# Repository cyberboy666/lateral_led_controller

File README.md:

# lateral_led_controller

### hardware network controller for addressable led installations 

- this circuit is distributed by __UNDERSCORES__ - _an open video hardware label_ : it is available to purchase - as a pcb, kit or assembled unit - at [underscores.shop](https://underscores.shop/lateral_led_controller/)
- the schematic for the circuit can be found [here](/hardware/schematic.pdf)
- the pcb gerber files for the lastest version can be found [here](/hardware/gerber_latest.zip)
- interactive BOM is [here](https://htmlpreview.github.io/?https://github.com/cyberboy666/lateral_led_controller/blob/main/hardware/bom/ibom.html)
- consider [donating](https://opencollective.com/underscores) to the underscores project to help us continue creating for the commons

## description

_lateral_led_controller_ is a hardware interface that converts [Art-Net](https://art-net.org.uk/), a network protocol for transmitting DMX data over network, into signals that drive addressable LEDs. it can be combined with mapping software (such as my [artnet_led_mapper](https://github.com/cyberboy666/artnet_led_mapper/)) to send arbitrary video onto an led strip canvas

features include:

- receives artnet data via ETHERNET, WIFI or ACCESS_POINT
- natively drive addressable leds [WS281X](https://www.aliexpress.com/item/4001322411818.html) and [APA102](https://www.aliexpress.com/item/32322326979.html)
- supports up to `8` parallel data outs and up to `12` DMX universes for max control over `2000` leds !
- local web interface for easily configuring network / led settings
- flexible dc power input - between 5v to 12v with low-heat / efficient on-board step-down converter
- open source hardware and firmware - can be customized to meet your specific needs

## background

this controller is a companion to my [artnet_led_mapper](https://github.com/cyberboy666/artnet_led_mapper/) application that converts a video feed into artnet for addressable led strip installations. it was built for [lateral movement](https://cyberboy666.com/lateralmovement/) club nights such as seen here:

you can find some more background on this install and process here: [WORKS IN PROGRESS 04 - talk about controlling addressable leds for art installation](https://videos.scanlines.xyz/w/p/tUhDfYqJJPfjovscNMvFRL) 

## demo video

## hardware options

<details><summary>hardware options</summary>

besides this controller there are some more bits of hardware you will need to realize an _addressable led installation_ - i will outline some suggestions here based on my experience but this will depend on your specific requirements - feel free to [email me](mailto:tim@cyberboy666.com) if you would like individual consulting on this.

### led strips

this controller is configured to support two types of addressable led strips (more can be added by firmware update):

### __WS281X__

ie [neopixels](https://www.adafruit.com/product/2541),  [WS2813 (5v) or WS2815 (12v)](https://www.aliexpress.com/item/4001322411818.html)

- these strips are cheapest - around 5usd for 60/m on aliexpress
- data to them is sent over a single wire (D) but is quite slow (around _800kbps_)
- this means that a maximum of around 240 of these leds can be addressed in series before the refresh rate drops below 30fps
- this controller is designed to be able to address up to 8 seperate WS281X led strips in parallel (outputs D0-D7 on board) for maximum 1920 number of leds in total

### __APA102__

ie [dotstar](https://www.adafruit.com/product/2574) ,  [SK9822](https://www.aliexpress.com/item/32322326979.html)

- these strips cost more - around 10usd for 60/m on aliexpress
- data to them is sent over two wires : ( __D__ata and __C__lock ) but is _very fast_ - (around _24Mbps_ )
- the controller is designed to address a single APA10 led strip by connecting D0 -> Data, D1 -> Clock
- at those speeds there is no need to have parrallel outputs can easily address 2000 leds in series (may need to look into power injection tho)
- they also claim to draw around 1/5 of the power as WS281X (i havnt tested this myself)

## power supply

we ended up using a switching power supply [like this](https://www.aliexpress.com/item/1005002843829663.html) 

- choose voltage based on your strip type (likely to be either 5v or 12v)
- and then power based on the requirement for total number of leds you are using
- you should power the _lateral_led_controller_ from the same supply thats powering the leds (its designed to safely take 5v - 12v input) or atleast ensure the GNDs are connected
- take note on the recommended power wire thickness based on how much current is passing through it (if you use 12v strips then less current is required and therefore thinner wires)

## light diffusers

for most installation settings it is prefered to use some kind of diffuser to help to evenly distribute light. there are many options and information about this topic online

## wiring and connectors

the data lines from _lateral_led_controller_ uses Pluggable Screw Terminals - standard wire (22awg etc) can connect these lines from controller to the strip

theres also the option to use cat5/6 cables to carry multiple data lines from the _lateral_led_controller_ - these are quite cheap, come in long distances and have twisted pairs which should allow for longer runs

personally i prefer running power lines seperately (on [red+black paired wire](https://www.aliexpress.com/item/4000625095039.html) ) - and using [these kinds](https://www.aliexpress.com/item/1005004267277214.html) of barrel / screw connectors to easily plug in / unplug from the installation

most led strips come with these [SM JST 4](https://www.aliexpress.com/item/1005002516911742.html?) connectors pre-soldered to both ends. one option if you dont want to resolder wires / new connectors onto each strip would be to just get some extra of these and create breakouts

### custom adapter boards

i made two little pcb adatpers that may help you with format convertion also - see below for some examples of how you could wire them

</details>

## software options

<details><summary>software options</summary>

any software that can output artnet over a network can be used with _lateral_led_controller_. some programs i have tested it with include:

- my [artnet_led_mapper](https://github.com/cyberboy666/artnet_led_mapper) application
- [resolume](https://resolume.com/)
- [touch designer](https://derivative.ca/UserGuide/TouchDesigner)
- [QLC+](https://www.qlcplus.org/)

</details>

# documentation

this project is fully _open-source hardware_ - all the files required to build it are included in this repo for free. if you have the time and/or skill you can contribute back by collaborating on / testing new designs, improving these docs, making demo videos/other creative content etc. you can also support the project financially by [donating](https://opencollective.com/underscores) directing, or purchasing through the [web shop](https://underscores.shop).

depending on whether you are going fully diy or buying an assembled and tested unit, some of the following guides will be relavent to you. the flow would be:

## ordering parts

<details><summary><b>parts sourcing guide (w/ notes on pcb fabracation )</b> - start here if you are building fully from scatch or have purchased a pcb</summary>

i try to source all the parts i can from either:
- [tayda](https://www.taydaelectronics.com/) ; cheaper for common parts like resistors etc, also good for mechanical parts like switches and buttons
- [mouser](https://www.mouser.de/) ; has lots more options, speciality video ic's, can sometimes cost more (free shipping on orders over 50euros)
- other ; ocationally there will be parts which will need to be sourced elsewhere - usaully either aliexpress, ebay or amazon etc...

take a look at the [full_bom](/hardware/bom/full_bom.csv) for this project to see where i am sourcing each part from

## import into tayda

- go to the [tayda quick order](https://www.taydaelectronics.com/quick-order/) and in bottom corner choose _add from file_
- select the file [tayda_bom.csv](./hardware/bom/tayda_bom.csv) in the BOM folder (you will have to download it first or clone this repo)
- after importing select _add to cart_
- __NOTE:__ the minimum value for resistors is 10, so you may need to modify these values to add to cart (or if they are already modified here you will need to see the  full_bom for actual part QTY) 

- OPTIONAL: it is a good idea to add some dip-ic sockets and 2.54pin headers/sockets to your tayda order if you dont have them around already

## sourcing other parts

this circuit has a few _specific_ parts that can not be sourced from tayda/mouser:

### WT32-ETH01 micro-controller
we are using a [WT32-ETH01](https://www.aliexpress.com/item/1005007279607510.html) ESP32 controller with the LAN8720A chip / ethernet port already attached - this is because it requires specific routing that is easier to get in a module like this - [heres](https://github.com/egnor/wt32-eth01) some more general info about this uC - it should be easy to find with a search on ali/amazon/ebay/etc - if you get it without header pins you can solder the controller straight on to the pcb (using the castellated edges) 

### MP1584EN_5v_stepdown

another pre-soldered module used in this circuit is this [MP1584EN_5v_stepdown](https://www.aliexpress.com/item/1005006005888518.html) - 3A Step-down 5v

its a useful module that allows a wide range of voltage inputs and is much more efficent than standard linear regulators (so producing less heat - which is important for installation work) - you can also solder the board directly onto our pcb with the castellated edges - take note of the direction indicated by arrow on bottom of module

### WeMos_CH340G_USB_to_SERIAL

since the WT32-ETH01 doesnt have an on-board _usb-to-serial_ on the module for uploading firmware this board is designed to work with this [WeMos_CH340G_USB_to_SERIAL](https://www.aliexpress.com/item/1005006642575408.html) one - we are using this because it outputs the command signals that allow for auto-uploading (so we dont need to manually switch to boot mode every time) - you may need to join some pads with solder on the module to select DTS mode for it to work

## terminal jacks

the footprints on the pcb for the data line outputs are spaced for __3.5MM__

- im using [KF2EDG RIGHT ANGLE 3.5MM PLUGGABLE](https://www.aliexpress.com/item/1005005511990041.html) terminals in my kits, but this is up to you - standard screw terminal (non-pluggable) like [this](https://www.aliexpress.com/item/1005001333343844.html) could also fit..

## ordering pcbs

you can support this project by buying individual pcbs from the [shop](https://underscores.shop). if you would rather have pcbs fabricated from gerbers directly the file you need is [here](/hardware/gerber_latest.zip)

- i get my pcbs fabricated from [jlcpcb](https://cart.jlcpcb.com/quote) - 5 is the minumum order per design
- upload the zip file with the `add gerber file` button
- the default settings are mostly fine - set the __PCB Qty__ and __PCB Color__ settings (you can check that the file looks correct with pcb veiwer)
- it may be best to combine orders with other pcbs you want to have fab'd since the shipping can cost more than the items - also orginising group buys is a good way to distribute the extra pcbs /costs 
  
i often use jlcpcb because they are reliable, cheap and give you an option of colours. remember though that the cheapest Chinese fab houses are not always the most ethical or environmently friendly - if you can afford it consider supporting local companies. 

  </details>
  
## assembly guide
  
<details><summary><b>assembly guide</b> - start here if you have purchased a diy kit</summary>

## interactive BOM for build guiding

follow this link to view the [interactive BOM](https://htmlpreview.github.io/?https://github.com/cyberboy666/lateral_led_controller/blob/main/hardware/bom/ibom.html)

## general solder advice

- remember to heat pad first (2-3seconds), then add solder, then continue to heat (1-2seconds)

- Checkout the web-comic [soldering is easy](https://mightyohm.com/files/soldercomic/FullSolderComic_EN.pdf) for more soldering advice

## order of assembly

- both the _WT32-ETH01_ controller and the _MP1584EN_5v_stepdown_ module can be soldered directly to the board using the castellated edges (if you would rather use pins/sockets this is fine also - just be aware you may need to use higher standoffs if also mounting a front panel) - these should be soldered before anything else

- next i would solder the resistors, capictors (take note of direction), diodes, transistors etc

- finally would finish with ic's and interface parts - sockets, buttons etc...

</details>

## firmware guide

<details><summary><b>firmware guide</b> - for editing the code & flashing it to your micro-controller</summary>
  
## flashing firmware onto the micro-controller
  
if you have got a kit from the shop the default firmware will be pre-configured - still it could be useful to know how to update firmware / customize your controller.
  
### install guide
  
all _underscores_ projects with micro-controllers use [platformio](https://platformio.org/) with [visual studio code](https://code.visualstudio.com/) to edit, flash and monitor the code.
  
- first download (and unzip) the code in this repo - easiest is [as a zip](https://github.com/cyberboy666/lateral_led_controller/archive/refs/heads/main.zip) or you can clone using git if you are comfortable with this
- next download, install and open [visual studio code](https://code.visualstudio.com/#alt-downloads)
- now open the extension tab within vscode on left vertical menu (or press ctrl-shift-x) and search for `platformio` to install this extension

- connect the micro-controller to computer via usb with the __WeMos_CH340G_USB_to_SERIAL__ port, open the software folder of this project (ctrl-k ctrl-o) in vscode and find the _platformio_ commands (either in left vertical menu under _platformio_ or little tick/arrow symbols along bottom blue bar) - `PlatformIO: Upload` should flash the default code to your micro-controller

</details>

</details>

## operating guide
  
<details><summary><b>operating guide</b> - start here if you have purchased an assembled unit</summary>

## access settings interface for first time

- power on the circuit by plugging in a 5-12v dc supply into the POWER IN
- using a computer / phone connect to the ACCESS_POINT created by the controller: default name `leds` pw `ledsleds` - you should see the blue _network connected_ led come on when you have connected to this network
- in a browser go to `http://leds.local` (also try `http://192.168.4.1` if that doesnt work ) - you should now see the web interface!
- from here you can set up which connection mode to use, see your controllers ip and also set which led protocol & layout to use - make sure the led settings (led type, number of data lines and number of leds per line ) reflect your installation setup.
- for most installation settings it will be preferable to use wired ethernet connection to send data into this controller - make sure the IP/SUBMASK/GATEWAY settings reflect the ethernet settings being used on the computer this controller is connecting to. __auto assign ethernet connection__ worked from my linux machine but i could not get windows to assign an ip (act as dhcp) - maybe there is some setting or maybe it needs to be done manually from some operating systems such as windows.

## reset button

### soft reset

on the controller board next to the `NETWORK CONNECTED` led is a `CONTROLLER RESET` button - pushing this will reboot the controller -> you should see the _network connected_ light go off for a momement while it resets

### hard reset

if you hold down the `CONTROLLER RESET` button for 5 seconds then release it you should see the `NETWORK CONNECTED` led flashing -> then short pressing the `CONTROLLER RESET` again from this mode will perform a __hard reset__ this means that the _NETWORK TYPE_ is reset back to __ACCESS_POINT__ and all settings are restored to default (you will need to connect to `leds` with pw `ledsleds` again to set up your controller)

this can be helpful if you accidently put the controller into a state with network settings that you can not access the page any more.

(if you get to the flashing led state but do not want to do a hard reset just power down the controller while flashing and your settings will not be wiped)

</details>

### more info

<details><summary><b>how the circuit works</b></summary>
  
[coming soon]
                                                                                                                             
</details>

<details><summary><b>contributing guide</b></summary>
  
if you would like to contribute back to these projects in some way but dont know how the best thing (for now) would be to reach out to me directly ( tim@cyberboy666.com or @cyberboy666 on scanlines forum) - i will be happy to help
  
</details>

## credits & more info

This circuit is distributed through UNDERSCORES – open video hardware label – visit [underscores.shop](https://underscores.shop) for more info

The pcb was designed using KICAD , the booklet was created in LibreOffice Draw

Everything from gerbers, cad files, panels and documentation is freely available online and distributed under CC-BY-SA / open-source licenses – help us contribute to the commons !

Ask any questions or start discussions related to this project on the [scanlines.xyz](https://scanlines.xyz) forum – an online community space dedicated to diy av / electronic media art

You can contact me directly at tim (at) cyberboy666 (dot) com 
Please get in touch if you are interested in hosting a workshop !

thanks to Tor for user testing + detailed feedback and suggestions + help with web interface design. thanks to the Lateral Movement Crew: Leo, Teesh, Wendy, Luke, Sean - for all the work into making these parties happen

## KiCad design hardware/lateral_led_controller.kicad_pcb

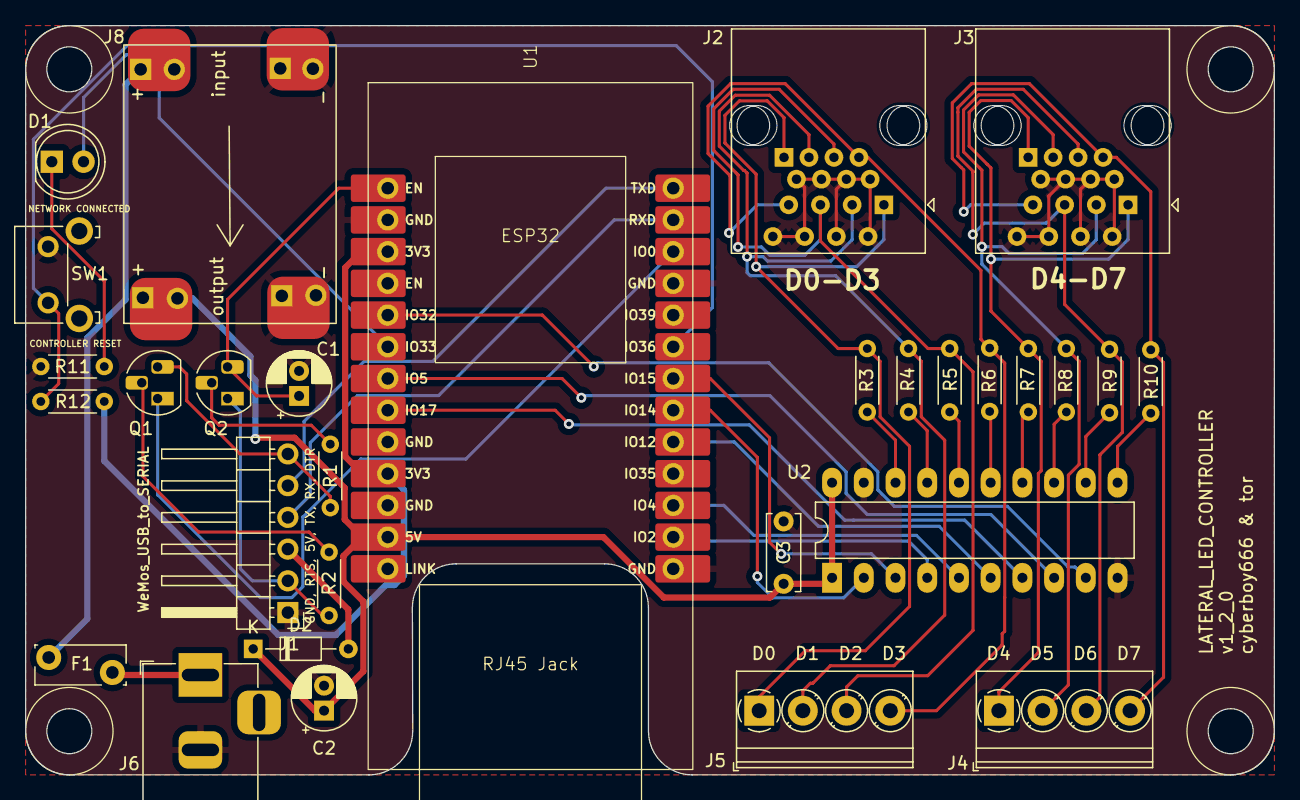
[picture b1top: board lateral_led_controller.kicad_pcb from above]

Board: 2 copper layers, 100.0 x 60.0 mm, 30 parts (0 on the bottom side), 41 nets.

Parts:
C1: 10u; CP_Radial_D5.0mm_P2.00mm
C2: 220u; CP_Radial_D5.0mm_P2.00mm
C3: 0.1u; C_Disc_D6.0mm_W2.5mm_P5.00mm
D1: LED; LED_D5.0mm
D2: 1n5819; D_DO-34_SOD68_P7.62mm_Horizontal
F1: Polyfuse; Fuse_Bourns_MF-RG300
J1: WeMos_CH340G_USB_to_SERIAL; PinHeader_1x06_P2.54mm_Horizontal
J2, J3: RJ45; RJ45_Horizontal
J4, J5: terminal_04; TerminalBlock_Phoenix_PT-1,5-4-3.5-H_1x04_P3.50mm_Horizontal
J6: Barrel_Jack_Switch; BarrelJack_Horizontal
J8: MP1584EN_5v_stepdown; MP1584EN_stepdown_module
Q1, Q2: 2N3904; TO-92_HandSolder
R1, R2, R12: 10k; R_Axial_DIN0204_L3.6mm_D1.6mm_P5.08mm_Horizontal
R3, R4, R5, R6, R7, R8, R9, R10, R11: 100; R_Axial_DIN0204_L3.6mm_D1.6mm_P5.08mm_Horizontal
SW1: SW_Push; SW_Tactile_SKHH_Angled
U1: WT32-ETH01
U2: 74HC245; DIP-20_W7.62mm_LongPads

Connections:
+3V3: R12.2, U1.3 (3.3V), U1.10 (3.3V)
+5V: C2.1, C3.1, D2.1 (K), J8.4, U1.12 (5V), U2.1 (A->B), U2.20 (VCC)
GND: C1.2, C2.2, C3.2, J1.1, J2.2, J2.4, J2.6, J2.8, J3.2, J3.4, J3.6, J3.8, J6.2, J8.2, J8.3, R11.1, SW1.2, U1.2 (GND), U1.9 (GND), U1.11 (GND), U1.14 (GND), U1.23 (GND), U2.10 (GND), U2.19 (CE)
unnamed: D1.2 (A), U1.6 (IO33/ADC1_CH5/TCH8)
unnamed: D1.1 (K), R11.2
unnamed: D2.2 (A), J1.3
unnamed: F1.1, J6.1
unnamed: J1.2, Q2.1 (E), R2.1
unnamed: J1.4, U1.25 (IO3/PRG_RX)
unnamed: J1.5, U1.26 (IO1/PRG_TX)
unnamed: J1.6, Q1.3 (C), R1.1
unnamed: J3.1, J4.1, R7.2
unnamed: J3.3, J4.2, R8.2
unnamed: J3.5, J4.3, R9.2
unnamed: J3.7, J4.4, R10.2
unnamed: J2.1, J5.1, R3.2
unnamed: J2.3, J5.2, R4.2
unnamed: J2.5, J5.3, R5.2
unnamed: J2.7, J5.4, R6.2
unnamed: F1.2, J8.1
unnamed: Q1.2 (B), R2.2
unnamed: Q1.1 (E), U1.24 (IO0/PRG_LOW/ETH_CLK)
unnamed: Q2.2 (B), R1.2
unnamed: C1.1, Q2.3 (C), U1.1 (CLK_EN)
unnamed: U1.15 (IO2/ADC2_CH2/TCH2/PRG_FLOAT_OR_GND), U2.4 (A2)
unnamed: U1.16 (IO4/ADC2_CH0/TCH0), U2.5 (A3)
unnamed: U1.7 (IO5/BOOT_FLOAT), U2.8 (A6)
unnamed: U1.18 (IO12/ADC2_CH5/TCH5/BOOT_FLOAT_OR_LOW), U2.6 (A4)
unnamed: U1.19 (IO14/ADC2_CH6/TCH6), U2.2 (A0)
unnamed: U1.20 (IO15/ADC2_CH3/TCH3), U2.3 (A1)
unnamed: U1.8 (IO17/UART2_TX), U2.7 (A5)
unnamed: U1.5 (IO32/ADC1_CH4/TCH9), U2.9 (A7)
unnamed: R12.1, SW1.1, U1.21 (IO36/ADC1_CH0/INPUT_ONLY)
unnamed: R3.1, U2.18 (B0)
unnamed: R4.1, U2.17 (B1)
unnamed: R5.1, U2.16 (B2)
unnamed: R6.1, U2.15 (B3)
unnamed: R7.1, U2.14 (B4)
unnamed: R8.1, U2.13 (B5)
unnamed: R9.1, U2.12 (B6)
unnamed: R10.1, U2.11 (B7)

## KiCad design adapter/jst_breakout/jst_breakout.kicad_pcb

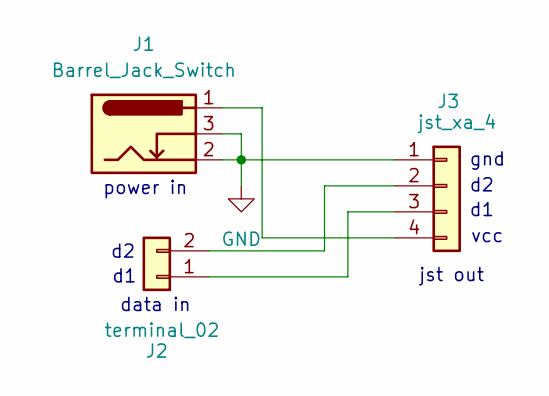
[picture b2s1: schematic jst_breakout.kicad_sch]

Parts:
J1: Barrel_Jack_Switch; BarrelJack_Horizontal
J2: terminal_02
J3: jst_xa_4; JST_XA_B04B-XASK-1-A_1x04_P2.50mm_Vertical

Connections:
GND: J1.2, J1.3, J3.1
unnamed: J2.1, J3.3
unnamed: J2.2, J3.2
unnamed: J1.1, J3.4

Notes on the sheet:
jst out
vcc
data in
power in
gnd

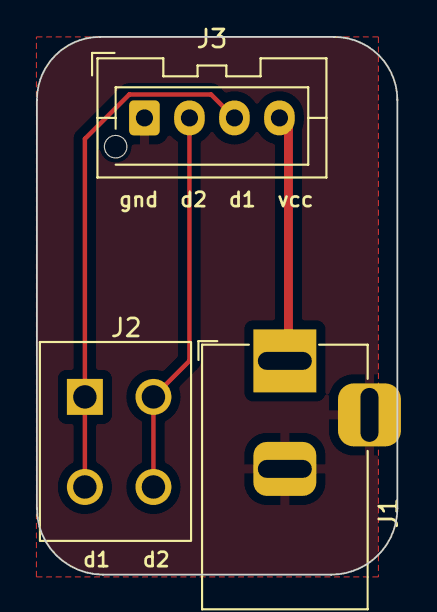
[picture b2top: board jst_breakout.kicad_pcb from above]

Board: 2 copper layers, 20.0 x 29.9 mm, 3 parts (0 on the bottom side), 4 nets.

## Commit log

2024-03-12 updating the code and circuit
2024-05-10 update hardware and software
2024-05-13 updating any changes in hre ?
2024-05-19 add git attributes
2024-05-21 Visual Tweaks
2024-05-21 Added kicad & affinity lockfiles to ignore
2024-05-23 updating hardware for v1_1_0 - change layouts etc
2024-07-05 updated board to use 4x terminal blocks
2024-08-01 update hardware to v1_1_0
2024-09-03 update hardware to v1_2_0
2024-09-03 rename the project
